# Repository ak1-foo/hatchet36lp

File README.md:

# hatchet36lp
original keyboard
- ortholinear
- 3 * 10 + 6
- kailh choc v1 switch

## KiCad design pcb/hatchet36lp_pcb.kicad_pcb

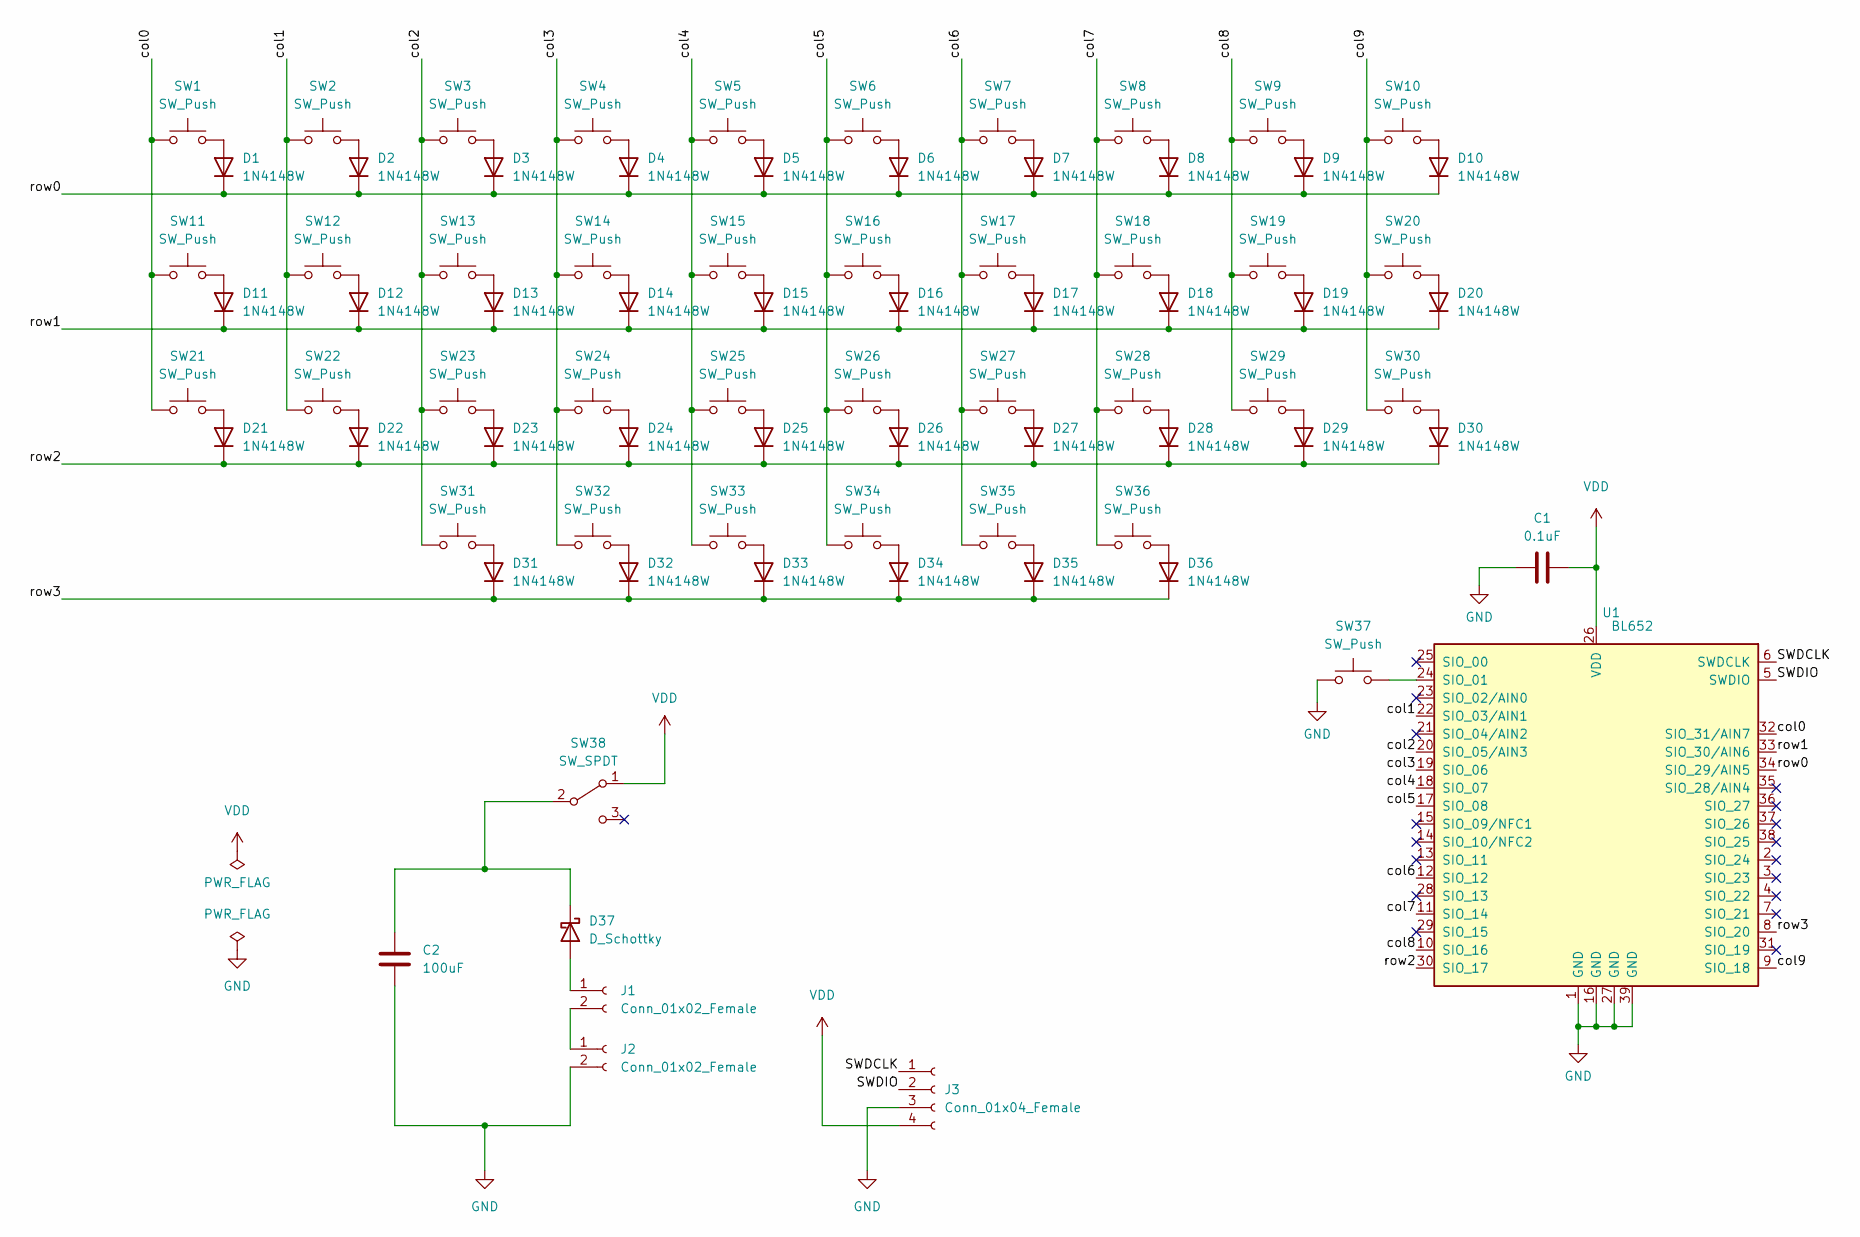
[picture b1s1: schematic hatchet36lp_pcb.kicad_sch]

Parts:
C1: 0.1uF; C_0805_2012Metric_Pad1.18x1.45mm_HandSolder
C2: 100uF; C_1206_3216Metric_Pad1.33x1.80mm_HandSolder
D1, D2, D3, D4, D5, D6, D7, D8, D9, D10, D11, D12, D13, D14, D15, D16, D17, D18, D19, D20, D21, D22, D23, D24, D25, D26, D27, D28, D29, D30, D31, D32, D33, D34, D35, D36: 1N4148W; D_SOD-123
D37: D_Schottky; D_SOD-323
J1, J2: Conn_01x02_Female; PinHeader_1x02_P2.00mm_Vertical
J3: Conn_01x04_Female; programming_port
SW1, SW2, SW3, SW4, SW5, SW6, SW7, SW8, SW9, SW10, SW11, SW12, SW13, SW14, SW15, SW16, SW17, SW18, SW19, SW20, SW21, SW22, SW23, SW24, SW25, SW26, SW27, SW28, SW29, SW30, SW31, SW32, SW33, SW34, SW35, SW36: SW_Push; Kailh-PG1350-1u-NoLED-mod
SW37: SW_Push; SW_SPST_ALPS-SKRP
SW38: SW_SPDT; SW_Slide_1P2T_CK_OS102011MS2Q_SmallPad
U1: BL652; Laird_BL652_LongPad

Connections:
/SWDCLK: J3.1, U1.6 (SWDCLK)
/SWDIO: J3.2, U1.5 (SWDIO)
/col0: SW1.1, SW11.1, SW21.1, U1.32 (SIO_31/AIN7)
/col1: SW2.1, SW12.1, SW22.1, U1.22 (SIO_03/AIN1)
/col2: SW3.1, SW13.1, SW23.1, SW31.1, U1.20 (SIO_05/AIN3)
/col3: SW4.1, SW14.1, SW24.1, SW32.1, U1.19 (SIO_06)
/col4: SW5.1, SW15.1, SW25.1, SW33.1, U1.18 (SIO_07)
/col5: SW6.1, SW16.1, SW26.1, SW34.1, U1.17 (SIO_08)
/col6: SW7.1, SW17.1, SW27.1, SW35.1, U1.12 (SIO_12)
/col7: SW8.1, SW18.1, SW28.1, SW36.1, U1.11 (SIO_14)
/col8: SW9.1, SW19.1, SW29.1, U1.10 (SIO_16)
/col9: SW10.1, SW20.1, SW30.1, U1.9 (SIO_18)
/row0: D1.1 (K), D2.1 (K), D3.1 (K), D4.1 (K), D5.1 (K), D6.1 (K), D7.1 (K), D8.1 (K), D9.1 (K), D10.1 (K), U1.34 (SIO_29/AIN5)
/row1: D11.1 (K), D12.1 (K), D13.1 (K), D14.1 (K), D15.1 (K), D16.1 (K), D17.1 (K), D18.1 (K), D19.1 (K), D20.1 (K), U1.33 (SIO_30/AIN6)
/row2: D21.1 (K), D22.1 (K), D23.1 (K), D24.1 (K), D25.1 (K), D26.1 (K), D27.1 (K), D28.1 (K), D29.1 (K), D30.1 (K), U1.30 (SIO_17)
/row3: D31.1 (K), D32.1 (K), D33.1 (K), D34.1 (K), D35.1 (K), D36.1 (K), U1.8 (SIO_20)
GND: C1.1, C2.2, J2.2, J3.3, SW37.1, U1.1 (GND), U1.16 (GND), U1.27 (GND), U1.39 (GND)
unnamed: C2.1, D37.1 (K), SW38.2 (B)
unnamed: D1.2 (A), SW1.2
unnamed: D2.2 (A), SW2.2
unnamed: D3.2 (A), SW3.2
unnamed: D4.2 (A), SW4.2
unnamed: D5.2 (A), SW5.2
unnamed: D6.2 (A), SW6.2
unnamed: D7.2 (A), SW7.2
unnamed: D8.2 (A), SW8.2
unnamed: D9.2 (A), SW9.2
unnamed: D10.2 (A), SW10.2
unnamed: D11.2 (A), SW11.2
unnamed: D12.2 (A), SW12.2
unnamed: D13.2 (A), SW13.2
unnamed: D14.2 (A), SW14.2
unnamed: D15.2 (A), SW15.2
unnamed: D16.2 (A), SW16.2
unnamed: D17.2 (A), SW17.2
unnamed: D18.2 (A), SW18.2
unnamed: D19.2 (A), SW19.2
unnamed: D20.2 (A), SW20.2
unnamed: D21.2 (A), SW21.2
unnamed: D22.2 (A), SW22.2
unnamed: D23.2 (A), SW23.2
unnamed: D24.2 (A), SW24.2
unnamed: D25.2 (A), SW25.2
unnamed: D26.2 (A), SW26.2
unnamed: D27.2 (A), SW27.2
unnamed: D28.2 (A), SW28.2
unnamed: D29.2 (A), SW29.2
unnamed: D30.2 (A), SW30.2
unnamed: D31.2 (A), SW31.2
unnamed: D32.2 (A), SW32.2
unnamed: D33.2 (A), SW33.2
unnamed: D34.2 (A), SW34.2
unnamed: D35.2 (A), SW35.2
unnamed: D36.2 (A), SW36.2
unnamed: D37.2 (A), J1.1
unnamed: J1.2, J2.1
unnamed: SW37.2, U1.24 (SIO_01)
VDD: C1.2, J3.4, SW38.1 (A), U1.26 (VDD)

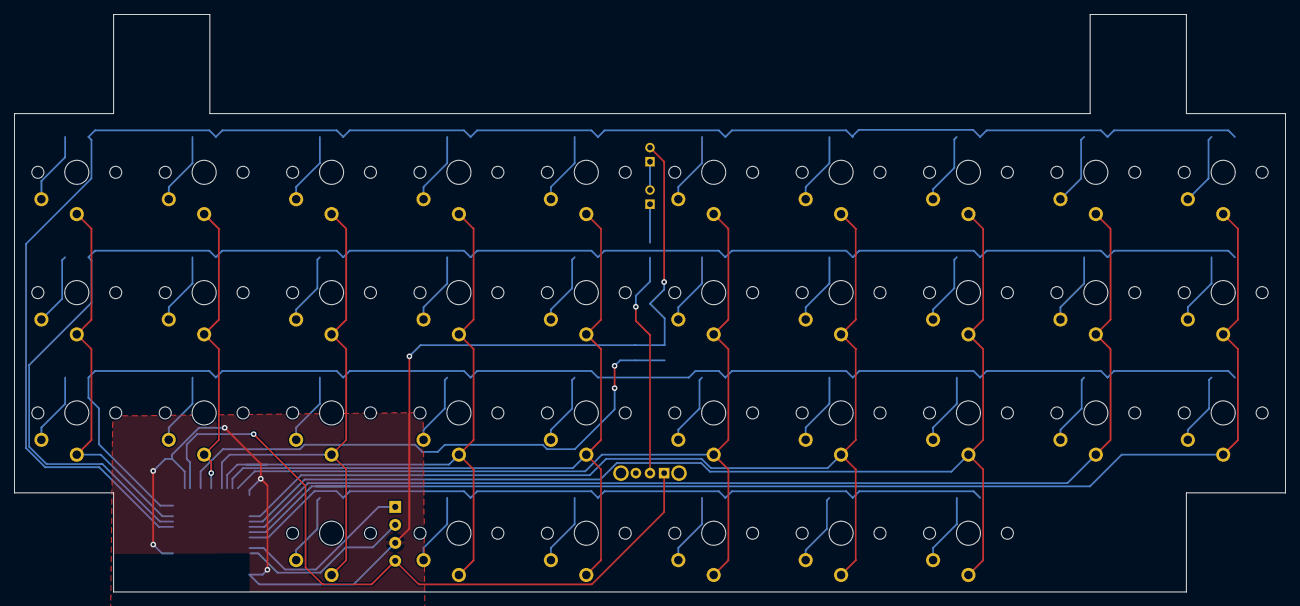
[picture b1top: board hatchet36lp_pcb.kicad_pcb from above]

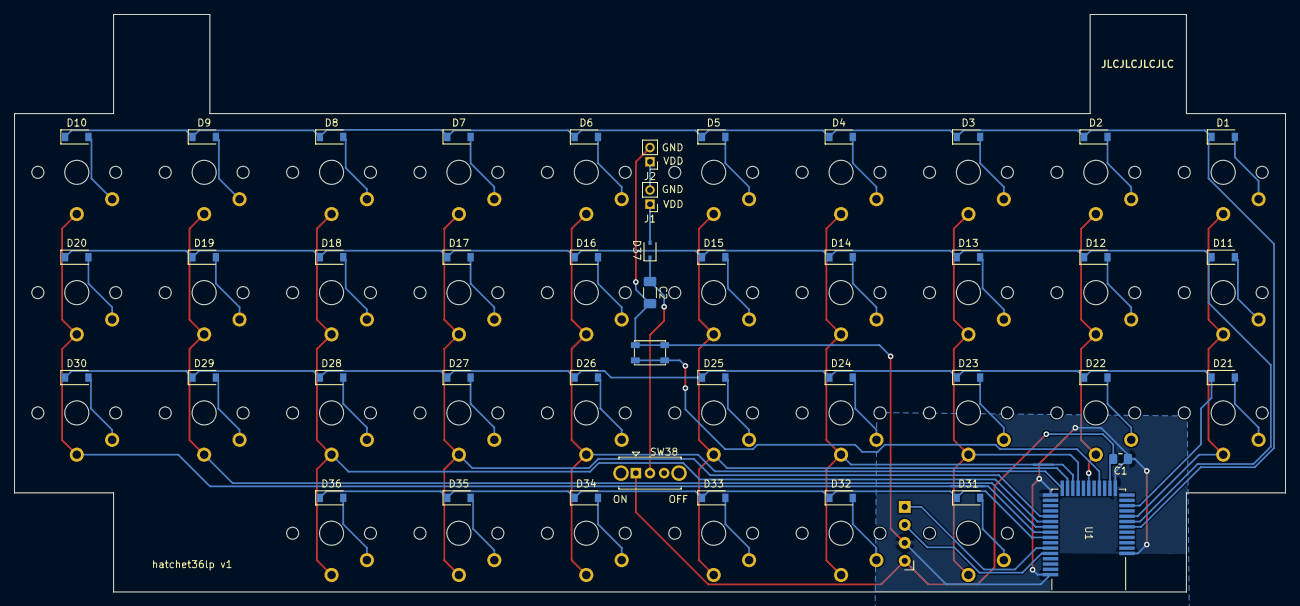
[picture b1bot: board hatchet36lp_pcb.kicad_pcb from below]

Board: 2 copper layers, 179.6 x 81.6 mm, 81 parts (45 on the bottom side), 58 nets.

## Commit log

2022-04-12 first commit, add schematic data
2022-04-12 annotate schematic symbol
2022-04-12 add submodule:Keeboi-Parts.pretty
2022-04-12 add submodule:Keebio-Parts.pretty
2022-04-12 add .gitignore : not track backup files
2022-04-15 mod path for unix, not for windows
2022-04-20 ignore backups
2022-04-20 add footprint of bl652 which has long pad
2022-04-20 assignment some footprint
2022-04-20 add some footprint to locallib
2022-04-20 align keys
2022-04-21 align diode
2022-04-21 add connector
2022-04-22 mod for two battery
2022-04-22 make 3d case data, just outline
2022-04-22 devided model
2022-04-23 put all parts on pcb
2022-04-23 made pcb which can work
2022-04-23 rename directory
2022-04-23 change location of test files
2022-04-23 change keyboard name, hatchet36 -> hatchet36lp
2022-04-23 rename kicad files, hatchet36_circuit_board -> hatchet36lp_pcb
2022-04-23 mod gitignore because i changed directory name of kicad backup files
2022-04-23 modify .gitmodules because i changed directory name of pcb
2022-04-23 add more info
2022-04-24 made case, but holes for screw don't exist yet
2022-04-24 made case, but screw don't exist
2022-04-24 shrink pcb 0.2mm to secure clearance
2022-04-26 made case, not devided yet
2022-04-26 split case
2022-04-26 mod silk for jlcpcb order
2022-04-26 case done!
2022-04-26 gen gerber
2022-04-27 modify pin
2022-04-27 made gerber files
2022-06-03 remove case data, because it has some dimensional error :(
